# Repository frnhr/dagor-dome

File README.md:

Dagor Dome
==========

IDE and code style guide
------------------------

### Code style guide ###

First, memorize this:   
**The Zen of Pyth.. Arduino! Arduino, yes.** And C, too.

    Beautiful is better than ugly.
    Explicit is better than implicit.
    Simple is better than complex.
    Complex is better than complicated.
    Flat is better than nested.
    Sparse is better than dense.
    Readability counts.
    Special cases aren't special enough to break the rules.
    Although practicality beats purity.
    Errors should never pass silently.
    Unless explicitly silenced.
    In the face of ambiguity, refuse the temptation to guess.
    There should be one-- and preferably only one --obvious way to do it.
    Although that way may not be obvious at first unless you're Dutch.
    Now is better than never.
    Although never is often better than *right* now.
    If the implementation is hard to explain, it's a bad idea.
    If the implementation is easy to explain, it may be a good idea.
    Namespaces are one honking great idea -- let's do more of those!
    
https://www.python.org/doc/humor/#the-zen-of-python

### C ⊂ C++ ###

"Arduino code" is C++, not (just) C. Even though a lot of Arduino sketches look like they are C-only, libraries are usually teeming with C++ features. 

In user code (i.e. the Arduino sketch) its ok to use C++ features, but always make sure  the code is readable for someone new to C++ as well as Arduino.

We are primarily working with hardware (registers, pins, etc), and this should be:
 * clearly visible in the code,
 * OR completely encapsulated (as most libraries do),
 * BUT NEVER something "in between".

##### Code style #####

###### TL;DR:

  * indent with 4 spaces
  * always use "{" and "}"
  * keep "{" inline everywhere except when declaring functions and classes - in those cases "{" should have a line of its own
  * cases:
    - variables: lowercase\_with_underscores
    - constants: UPPERCASE\_WITH_UDERSCORES
    - classes, types, structs: CamelCase
  * keep lines length in check! 80 chars is uber-strict, 100 is polite, 120 is ok, more is just bad. It just is. Really.

###### Details:

 * please refer to:
   - http://users.ece.cmu.edu/~eno/coding/CCodingStandard.html
   - https://www.kernel.org/doc/Documentation/CodingStyle
 * in that order, those two docs are not in agreement on everything

###### Global variables

Global variables are ok. Global classes and/or structs that replace several variables are even better.

###### Separation of concerns

One piece of code should only deal with one thing. The "piece" may be a file, a function, etc.

Different "pieces" should interact only via a well-defined interfaces - preferably state variables.

### Stino and Sublime Text 2 #########

**Stino** is a plugin for **Sublime Text 2** editor. It is simple to install and works more or less *outofthebox*.

#### Installation #####################

**Sublime Text 2** can be installed from http://www.sublimetext.com/2

**Stino** install instruction are localted here: https://sublime.wbond.net/installation#st2

### Eclipse

todo ... how to set it up?

### Why not the Arduino IDE ##############

It needs to be installed and set up, but it has several shortcomings that make it a substandard choice for non-trivial projects.

 * no code completion
 * global settings - when programming multiple boards settings need to be changed before each upload
 * poor code formatting
 * poor code coloring

## Code overview

todo ...  here come nice ASCII diagram of code and state buffers ...

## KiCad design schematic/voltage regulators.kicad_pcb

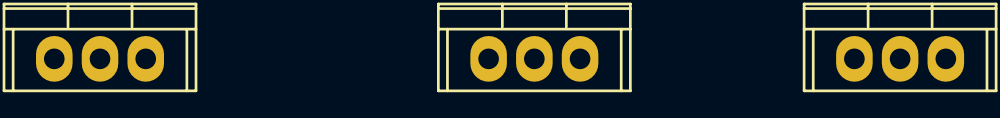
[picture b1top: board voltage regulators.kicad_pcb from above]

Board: 2 copper layers, 3 parts (0 on the bottom side), 3 nets, no tracks yet.

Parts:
U1, U2: 7810; TO-220
U3: 7805; TO-220

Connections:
+10V: U1.2, U2.3, U3.1
+24V: U1.1, U2.1
GND: U2.2, U3.2

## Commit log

2014-04-14 Initial source
2014-04-14 Komentari, bug fix (calibration_functions), kontroler ima glavnu rijec (motor_control) i dodan serial protocol.txt
2014-06-06 Python interface
    I nekoliko prilagodbi/promjena arduino koda
2014-06-11 radio kontrola vratiju
2014-06-11 Reset over RS-232
2014-06-22 IDE instructions to readme
2014-06-22 sublime text 2 project; stino settings gitignore
2014-06-22 some code cleanup; pins remapped for new connector shield; pullups enabled, disconnected state detection
2014-06-22 pullups; disconnected state detection; radio logic tweak
2014-06-22 auto code formatting
2014-12-13 Pins, baud rate
2014-12-13 bug hunting in serial comm code...
2014-12-13 allow manual movement over serial (up/down commands) after calibration
2014-12-13 dome.py settings & fixes
2014-12-13 debug=false
2014-12-13 new logic + cleaner code
2014-12-13 serial acknowledge
2014-12-13 bug hunting season
2014-12-13 cli - remote command "manual"
2014-12-14 refactor WIP
2014-12-14 pointerssss
2014-12-14 buggy reorganized code
2014-12-14 it compiles!
2014-12-16 Eclipse CDT
2014-12-27 code organizing; full decoupling; code style; all WIP
2015-07-24 requirements file
2015-07-25 THIS PREVENTED SUCCESSFULL UPLOADS TO MEGA!!!!
2015-07-25 to_string bugfix reset Arduino
2015-07-25 Calibration refactored
2015-07-29 Fixed calibration results
2015-07-29 Heartbeat led 13
2015-07-31 removed unused EEPROM.ino
2015-08-04 schematic
2015-08-04 Dont need to_string for double
2015-08-04 Update current azimuth after calibration
2015-08-04 Debug prints, for testing connection stability
2015-08-04 map_to_circle retutn type double
2015-08-04 moved map_to_circle() to utils.h and fixed bug with types
2015-08-06 #define statements instead of consts, pin numbers are constants now, writing calibration to EEPROM and bug fix in last stage of calibration
2015-08-07 working calibration!!
2015-08-18 debug=false, switch_read_cycles=15 instead of 100, /dev/tty instead of COM
2015-09-22 human readable serial protocol, dome.py interface v1.1
2015-09-22 Removed ignored file
2016-05-08 Added coordinate fitting test
